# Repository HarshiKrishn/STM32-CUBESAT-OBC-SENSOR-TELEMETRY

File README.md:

# STM32 CubeSat OBC – Sensor Telemetry System

A custom-designed STM32-based On-Board Computer (OBC) for CubeSat applications with integrated sensor telemetry and power subsystem.

---

## 🚀 Overview

This project implements a CubeSat OBC built around STM32 microcontroller for:

- Sensor data acquisition
- Telemetry formatting
- Power subsystem integration
- Communication interface support

Designed completely in KiCad.

---

## 🧠 System Architecture

- MCU: STM32
- Power Regulation: 3.3V & 5V rails
- Communication:
  - UART
  - I2C
  - SPI
- Telemetry Output Support

---

## 🔌 Power Subsystem

- Battery input stage
- Voltage regulation
- Protection circuitry
- Filtering and decoupling

---

## 📡 Telemetry

- Sensor data acquisition
- Structured data formatting
- Ready for ground-station transmission

---

## 🖥️ Tools Used

- KiCad (Schematic + PCB)
- MATLAB (Validation)
- Proteus (Simulation)
- OnShape (Mechanical validation)

---

---

## 📂 Repository Structure

- `/Schematic`
- `/PCB`
- `/3D_Images`
- `/Docs`

---
## 3D PCB View

### Top View

### Bottom View

## 👤 Author

Designed and developed by Harshini  
Embedded Systems & PCB Design Enthusiast

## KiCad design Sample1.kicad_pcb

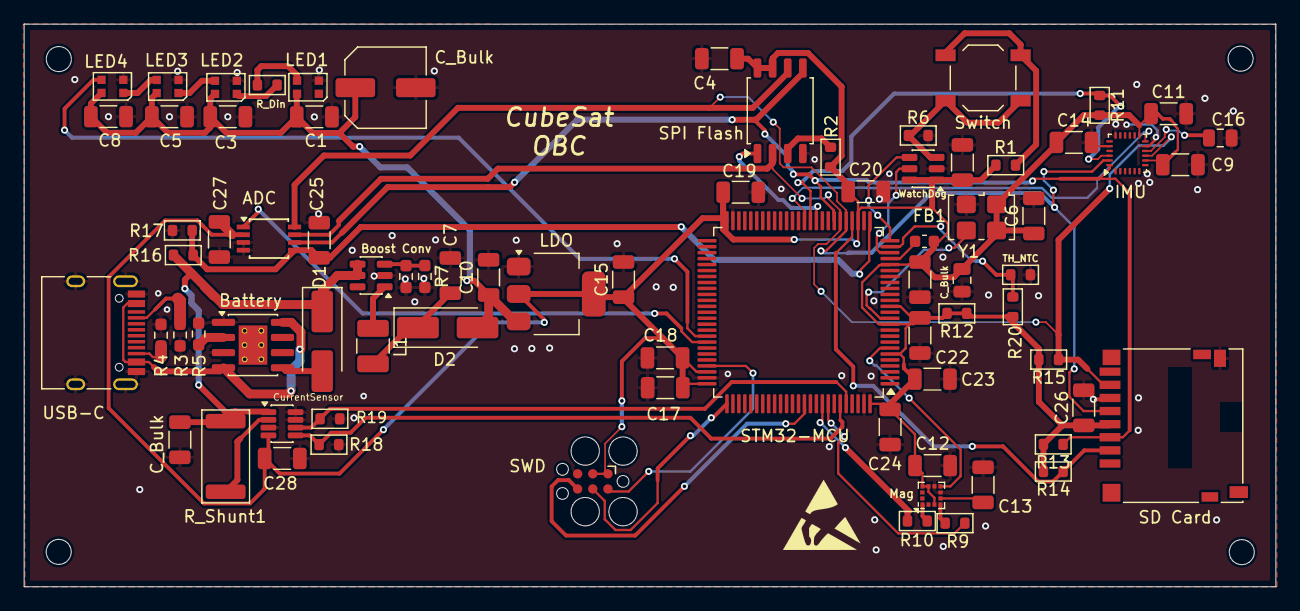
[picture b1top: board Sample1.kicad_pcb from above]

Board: 2 copper layers, 105.0 x 47.2 mm, 77 parts (0 on the bottom side), 47 nets.

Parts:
ADC: ADC082S021; TSSOP-8_3x3mm_P0.65mm
Battery: TP4056-42-ESOP8; SOIC-8-1EP_3.9x4.9mm_P1.27mm_EP2.41x3.3mm_ThermalVias
Boost Conv: MT3608; SOT-23-6
C1, C2, C3, C5, C6, C8, C11, C12, C13, C14, C17, C18, C19, C20, C21, C22, C23, C25, C27, C28: 100nF; C_1206_3216Metric
C4, C9, C26: 1uF; C_1206_3216Metric
C7: 22µF; C_1206_3216Metric
C10, C15, C24: 10uF; C_1206_3216Metric
C16: 2.2uF; C_0805_2012Metric
C_Bulk: 100uF; C_1206_3216Metric
C_Bulk#2: 100uF; C_Elec_6.3x5.4
C_Bulk#3: 100uF; C_0805_2012Metric
CurrentSensor: INA219BxDCN; SOT-23-8
D1, D2: SS14; D_SMA_Handsoldering
FB1: Ferrite_Bead; Fuse_0603_1608Metric
IMU: ICM-20948; InvenSense_QFN-24_3x3mm_P0.4mm
L1: 10µH; L_1210_3225Metric_Pad1.42x2.65mm_HandSolder
LDO: AMS1117-3.3; SOT-223-3_TabPin2
LED1, LED2, LED3, LED4: WS2812B-2020; LED_WS2812B-2020_PLCC4_2.0x2.0mm
Mag: LIS2MDL; LGA-12_2x2mm_P0.5mm
R1, R11, R13, R14, R15, R20: 10k; R_0603_1608Metric
R2: 0; R_0603_1608Metric
R3, R4: 5.1k; R_0603_1608Metric_Pad0.98x0.95mm_HandSolder
R5: 2.4k; R_0603_1608Metric_Pad0.98x0.95mm_HandSolder
R6: 8.85k; R_0603_1608Metric
R7: 75k; R_0603_1608Metric_Pad0.98x0.95mm_HandSolder
R8: 10k; R_0603_1608Metric_Pad0.98x0.95mm_HandSolder
R9, R10, R18, R19: 4.7K; R_0603_1608Metric
R12: 10K; R_0603_1608Metric
R16: 100K; R_0603_1608Metric
R17: 33K; R_0603_1608Metric
R_Din: 330; R_0603_1608Metric
R_Shunt1: 0.1; R_2512_6332Metric
SD Card: Micro_SD_Card; microSD_HC_Hirose_DM3D-SF
SPI Flash: W25Q16JVSS; SOIC-8_5.3x5.3mm_P1.27mm
STM32-MCU: STM32L496VGTx; LQFP-100_14x14mm_P0.5mm
SWD: Conn_ARM_SWD_TagConnect_TC2030; Tag-Connect_TC2030-IDC-FP_2x03_P1.27mm_Vertical
Switch: SW_Push; SW_SPST_TL3342
TH_NTC: 10K@25degreeC; R_0603_1608Metric
USB-C: USB_C_Receptacle_PowerOnly_24P; USB_C_Receptacle_HRO_TYPE-C-31-M-12
WatchDog: TPL5010; SOT-23-6
Y1: SG-5032CAN; Oscillator_SMD_SeikoEpson_SG8002LB-4Pin_5.0x3.2mm

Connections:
/3V3: ADC.2 (V_{A}), C2.1, C4.1, C6.1, C9.1, C11.1, C12.1, C14.1, C15.1, C17.1, C18.1, C19.1, C20.1, C21.1, C22.1, C23.1, C24.1, C26.1, C27.1, C28.1, C_Bulk#3.1, CurrentSensor.4 (VS), FB1.2, IMU.8 (VDDIO), IMU.13 (VDD), LDO.2 (VO), Mag.3 (~CS), Mag.9 (Vdd), Mag.10 (Vdd_IO), R1.1, R2.1, R11.2, R12.1, R12.2, R13.2, R14.2, R15.2, R20.1, SD Card.4 (VDD), SPI Flash.7 (~HOLD/~RESET/IO_{3}), SPI Flash.8 (VCC), STM32-MCU.6 (VBAT), STM32-MCU.11 (VDD), STM32-MCU.14 (NRST), STM32-MCU.21 (VREF+), STM32-MCU.28 (VDD), STM32-MCU.50 (VDD), STM32-MCU.73 (VDDUSB), STM32-MCU.75 (VDD), STM32-MCU.100 (VDD), SWD.1 (VCC), SWD.3 (~RESET), WatchDog.1 (VDD), WatchDog.6 (~RST), Y1.1 (~ST), Y1.4 (VCC)
/5V: C1.1, C3.1, C5.1, C8.1, C10.1, C_Bulk#2.1, D2.2 (A), LDO.3 (VI), LED1.4 (VDD), LED2.4 (VDD), LED3.4 (VDD), LED4.4 (VDD)
/ADC_CS: ADC.1 (~CS), STM32-MCU.68 (PA9)
/Debug LEDs: LED4.3 (DIN), STM32-MCU.67 (PA8)
/EPS_O/P: Boost Conv.4 (EN), Boost Conv.5 (IN), C_Bulk.1, CurrentSensor.1 (IN+), D1.1 (K), R16.2, R_Shunt1.2
/EPS_V_ADC: ADC.5 (IN1), C25.1, R16.1, R17.1, STM32-MCU.26 (PA3)
/EXTI: Mag.7 (DRDY), STM32-MCU.7 (PC13)
/Flash_CS: SPI Flash.1 (~CS), STM32-MCU.35 (PB0)
/HSE_IN: STM32-MCU.12 (PH0), Y1.3 (OUT)
/I2C_SCL: R10.1, STM32-MCU.92 (PB6)
/I2C_SDA: R9.2, STM32-MCU.93 (PB7)
/IMU_CS: IMU.22 (~CS), R11.1, STM32-MCU.36 (PB1)
/IMU_INT: IMU.12 (INT1), STM32-MCU.37 (PB2)
/MCU_DONE: STM32-MCU.25 (PA2), WatchDog.4 (DONE)
/MCU_WAKE: STM32-MCU.23 (PA0), WatchDog.5 (WAKE)
/SCL: CurrentSensor.5 (SCL), R18.1, STM32-MCU.95 (PB8)
/SDA: CurrentSensor.6 (SDA), R19.2, STM32-MCU.96 (PB9)
/SD_CS: R14.1, SD Card.2 (DAT3/CD), STM32-MCU.29 (PA4)
/SPI1_MISO: ADC.7 (DOUT), IMU.9 (SDO/AD0), R15.1, SD Card.7 (DAT0), SPI Flash.2 (DO/IO_{1}), STM32-MCU.31 (PA6)
/SPI1_MOSI: ADC.6 (DIN), IMU.24 (SDA/SDI), R13.1, SD Card.3 (CMD), SPI Flash.5 (DI/IO_{0}), STM32-MCU.32 (PA7)
/SPI1_SCK: ADC.8 (SCLK), IMU.23 (SCL/SCLK), SD Card.5 (CLK), SPI Flash.6 (CLK), STM32-MCU.30 (PA5)
/SWCLK: STM32-MCU.76 (PA14), SWD.4 (SWCLK)
/SWDIO: STM32-MCU.72 (PA13), SWD.2 (SWDIO)
/SWO: STM32-MCU.89 (PB3), SWD.6 (SWO)
/Temp_ADC: R20.2, STM32-MCU.24 (PA1), TH_NTC.1
GND: ADC.3 (GND), ADC.4 (IN2), Battery.1 (TEMP), Battery.3 (GND), Boost Conv.2 (GND), C1.2, C2.2, C3.2, C4.2, C5.2, C6.2, C7.2, C8.2, C9.2, C10.2, C11.2, C12.2, C13.2, C14.2, C15.2, C16.2, C17.2, C18.2, C19.2, C20.2, C21.2, C22.2, C23.2, C24.2, C25.2, C26.2, C27.2, C28.2, C_Bulk.2, C_Bulk#2.2, C_Bulk#3.2, CurrentSensor.3 (GND), CurrentSensor.7 (A0), CurrentSensor.8 (A1), IMU.11 (FSYNC), IMU.18 (GND), IMU.20 (GND), LDO.1 (GND), LED1.2 (VSS), LED2.2 (VSS), LED3.2 (VSS), LED4.2 (VSS), Mag.6 (GND), Mag.8 (GND), R3.1, R4.1, R5.2, R6.2, R7.2, R8.2, R17.2, R18.2, R19.1, SD Card.6 (VSS), SD Card.9 (SHIELD), SPI Flash.4 (GND), STM32-MCU.10 (VSS), STM32-MCU.19 (VSSA), STM32-MCU.20 (VREF-), STM32-MCU.27 (VSS), STM32-MCU.49 (VSS), STM32-MCU.74 (VSS), STM32-MCU.99 (VSS), SWD.5 (GND), TH_NTC.2, USB-C.A1 (GND), USB-C.A12 (GND), USB-C.B1 (GND), USB-C.B12 (GND), USB-C.S1 (SHIELD), WatchDog.2 (GND), Y1.2 (GND)
unnamed: Battery.5 (BAT), D1.2 (A)
unnamed: C7.1, D2.1 (K), L1.2
unnamed: R4.2, USB-C.A5 (CC1)
unnamed: R3.2, USB-C.B5 (CC2)
unnamed: LED1.3 (DIN), R_Din.2
unnamed: LED2.3 (DIN), LED3.1 (DOUT)
unnamed: LED2.1 (DOUT), R_Din.1
unnamed: LED3.3 (DIN), LED4.1 (DOUT)
unnamed: R1.2, Switch.2
unnamed: R2.2, SPI Flash.3 (~WP/IO_{2})
unnamed: R6.1, Switch.1, WatchDog.3 (DELAY/M_RST)
unnamed: Battery.4 (V_{CC}), Battery.8 (CE), USB-C.A4 (VBUS), USB-C.A9 (VBUS), USB-C.B4 (VBUS), USB-C.B9 (VBUS)
unnamed: Battery.2 (PROG), R5.1
unnamed: Boost Conv.3 (FB), R7.1, R8.1
unnamed: Boost Conv.1 (SW), L1.1
unnamed: C13.1, Mag.5 (C1)
unnamed: Mag.1 (SCL/SPC), R10.2
unnamed: Mag.4 (SDA/SDI/SDO), R9.1
unnamed: C16.1, IMU.10 (REGOUT)
unnamed: FB1.1, STM32-MCU.22 (VDDA)
unnamed: CurrentSensor.2 (IN-), R_Shunt1.1

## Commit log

2026-02-19 Initial commit - STM32 CubeSat OBC Sensor Telemetry PCB
